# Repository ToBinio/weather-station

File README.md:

# WeatherStation

## External Unit

### Sensors
- Temperature
- CO2
- Humidity
- Pressure
- Wind Speed
- Rainfall
- UV Index

### Features
- SolarPower
- HomeAssistant integration (mqtt)

## Indoor Unit

### Sensors
- Temperature
- CO2
- Humidity
- Volatile Organic Compounds (VOC / TVOC)
- Pressure
- Particulate Matter (PM1.0 / PM2.5 / PM10)

### Features
- Power plug
- Display
- HomeAssistant integration (mqtt)

## Shopping List
- [esp32](https://www.amazon.de/dp/B0D9BTQRYT?ref=cm_sw_r_cp_ud_dp_T5XN0CJ66ND8A965GBN2&social_share=cm_sw_r_cp_ud_dp_T5XN0CJ66ND8A965GBN2)
- [display](https://www.amazon.de/-/en/AZDelivery-HD44780-Bundle-Characters-Compatible/dp/B07JH6GHPR?s=ce-de)
- [pinHeaders](https://www.amazon.de/-/en/Breakaway-Connector-Soldering-Arduino-Prototype/dp/B0DRCL1MZ3)

### Sensors
- [SCD41(CO2)](https://www.amazon.de/dp/B0FK53SJHB?ref=cm_sw_r_cp_ud_dp_MKT09AE6P4V9VANQQ0NB&social_share=cm_sw_r_cp_ud_dp_MKT09AE6P4V9VANQQ0NB)
- [BME680(temp, humidity, pressure, VOC)](https://www.amazon.de/-/en/Development-CJMCU-680-Temperature-Interface-Compatible/dp/B0FPRC1FXW)

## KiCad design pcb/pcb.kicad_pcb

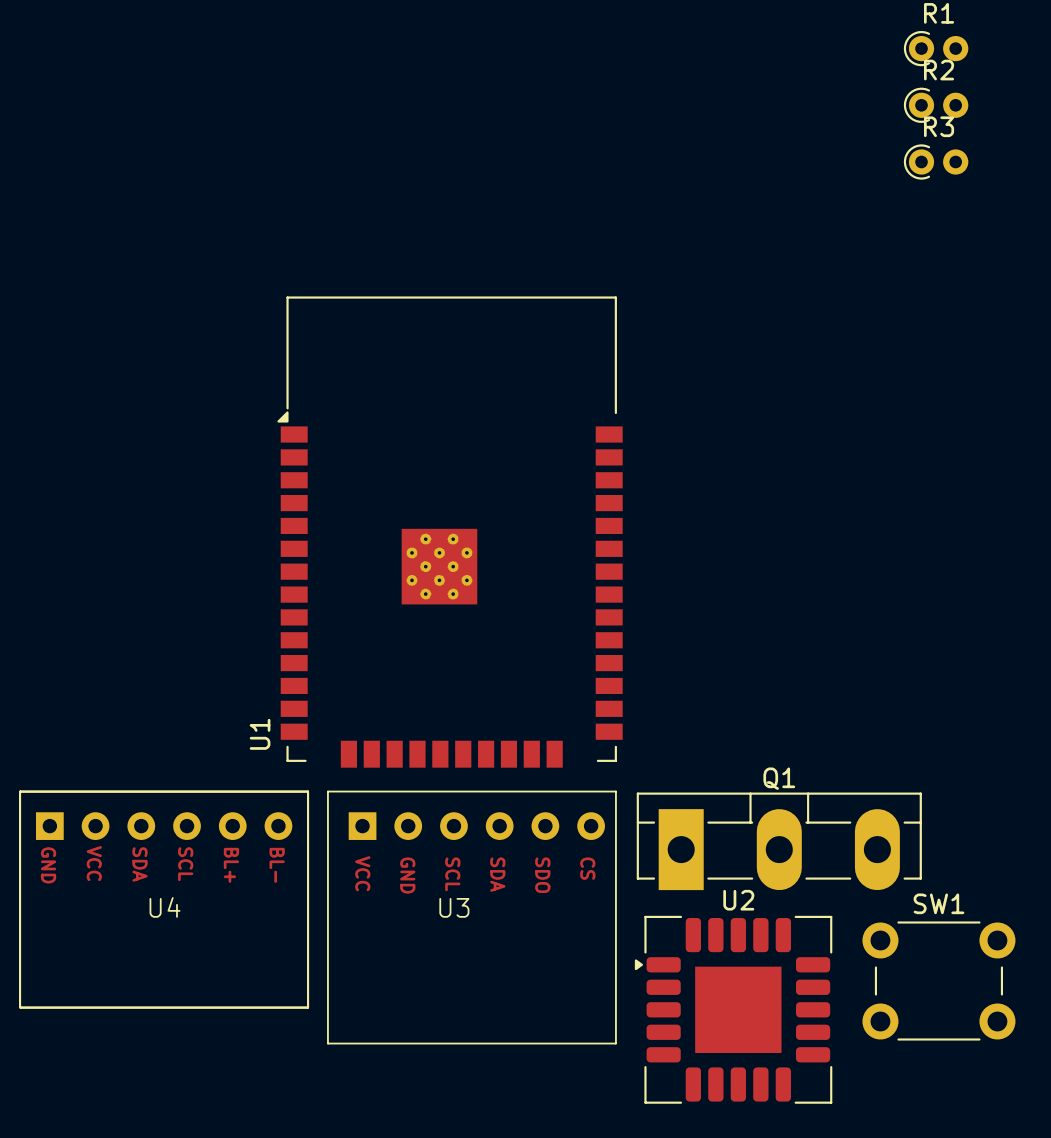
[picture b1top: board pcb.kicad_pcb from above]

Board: 2 copper layers, 9 parts (0 on the bottom side), 12 nets, no tracks yet.

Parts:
Q1: PNP; TO-3P-3_Vertical
R1: R_Photo; R_Axial_DIN0204_L3.6mm_D1.6mm_P1.90mm_Vertical
R2: 1m; R_Axial_DIN0204_L3.6mm_D1.6mm_P1.90mm_Vertical
R3: 2k; R_Axial_DIN0204_L3.6mm_D1.6mm_P1.90mm_Vertical
SW1: SW_Push; SW_PUSH_6mm
U1: ESP32-WROOM-32
U2: SCD41-D-R2; Sensirion_SCD4x-1EP_10.1x10.1mm_P1.25mm_EP4.8x4.8mm
U3: BME680
U4: 1602A_LCD_I2C; LCD_I2C

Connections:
+3.3V: Q1.3 (E), R1.1, U2.7 (VDD), U2.19 (VDD), U3.1 (VCC)
+5V: U1.2 (VDD), U4.2 (VCC)
GND: R2.2, SW1.2, U1.1 (GND), U1.15 (GND), U1.38 (GND), U1.39 (GND), U2.6 (GND), U2.20 (GND), U2.21 (GND), U3.2 (GND), U4.1 (GND)
unnamed: Q1.2 (B), R3.2
unnamed: Q1.1 (C), U4.6 (BL-)
unnamed: R3.1, U1.31 (IO19)
unnamed: U1.33 (IO21), U2.10 (SDA), U3.4 (SDA)
unnamed: U1.36 (IO22), U2.9 (SCL), U3.3 (SCL)
unnamed: SW1.1, U1.37 (IO23)
unnamed: U1.10 (IO25), U4.3 (SDA)
unnamed: U1.11 (IO26), U4.4 (SCL)
unnamed: R1.2, R2.1, U1.8 (IO32)

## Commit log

2025-12-23 slightly update readme
2025-12-24 update shopping list
2025-12-24 scaffold project
2025-12-25 simple bme680 data gathering and lcd display
2025-12-26 add simple electric schematic
2025-12-26 add pullup resistors to design
2025-12-30 update pcb design to split 5v and 3.3v i2c devices
2025-12-30 dont commit pcb-backups
2025-12-30 init non esp-idf project
2025-12-31 blinking led
2025-12-31 read sensor data
2025-12-31 display temp
2025-12-31 add button for selecting displayMode
2026-01-01 fix pressure unit
2026-01-01 init display on first startup
2026-01-01 run async where possible
2026-01-01 connect to wifi
2026-01-03 publish updates to ha
2026-01-04 use log crate
2026-01-04 disallow unwrap()
2026-01-10 add brighness reader
2026-01-14 basic setup pwm for backlight
2026-01-15 try dimming backlight via pwm
2026-01-15 fix PWM issues
2026-01-15 simplify schema by only using 3.3V
2026-01-17 Revert "simplify schema by only using 3.3V"
    This reverts commit 0584054847f7e7c6e520f649ccfa9b452367a544.
2026-01-17 working backlight dimming
2026-01-18 remove unneeded info log
2026-02-24 add basic box
2026-02-25 add holder vor main board
2026-02-28 move to stable for embassy-ha
2026-04-17 start pcb setup
